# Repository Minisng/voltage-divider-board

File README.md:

[프로젝트 보고서] Voltage Divider Board Design & Simulation
1. Project Overview (프로젝트 개요)
목적: 10V DC 입력 전원을 받아 안정적인 2V DC 전압을 출력하는 전압 분배 회로 설계 및 PCB 제작 데이터 구축
주요 사양:
Input Voltage ($V_{in}$): 10V DC
Target Output Voltage ($V_{out}$): 2.0V DC
Load Resistance ($R_1, R_2$): $R_1 = 8\text{k}\Omega$, $R_2 = 2\text{k}\Omega$
사용 툴: LTspice (Simulation), KiCad 8.0 (Schematic & Layout)
2. Circuit Theory & LTspice Simulation (시뮬레이션 및 검증)
① 전압 분배 수식 검증
$$V_{out} = V_{in} \times \frac{R_2}{R_1 + R_2} = 10\text{V} \times \frac{2\text{k}\Omega}{8\text{k}\Omega + 2\text{k}\Omega} = 2.0\text{V}$$
② LTspice Transient Analysis
시뮬레이션 조건: .tran 1s (1초간 과도 응답 관찰)
결과분석: 10V DC 입력 조건에서 $V_{out}$ 노드가 오차 없이 정확히 2.0000V로 수렴함을 확인.
[첨부 1]: LTspice 회로도 및 파형 캡처 이미지 (앞서 캡처한 V(vout) = 2.0V 빨간선 그래프 이미지)
3. KiCad Schematic & PCB Layout (회로도 및 PCB 설계)
① Schematic Design
외부 전원 연결용 커넥터(J1, J2 2-Pin Header) 추가 및 ERC(Electrical Rules Check) 통과
Net Label (Vout) 설정을 통한 노드 식별성 강화
② PCB Layout Specifications
Board Dimensions: 2-Layer PCB (약 30mm x 20mm)
Component Footprints:
$R_1, R_2$: SMD 0805 Package
$J_1, J_2$: 2.54mm Pitch Pin Header
Copper Pour: Top/Bottom Layer 전체 GND Zone Fill (노이즈 방지)
DRC (Design Rules Check): 에러/미연결 패턴 0건 검수 완료
4. 3D Raytracing & Physical Verification (3D 검수 및 결과물)
[첨부 2]: KiCad 3D Viewer로 추출한 고화질 PCB 3D 렌더링 이미지 (Alt + 1 Top View, 사선 각도 뷰)
부품 배치 검수: 커넥터 및 저항 간 물리적 간섭(Clearance) 없음 확인
5. Deliverables (최종 산출물 목록)
Schematic & PCB File: KiCad 프로젝트 원본 파일
Gerber & Drill Files: 제조 공장 발주용 표준 데이터 (Gerber_VoltageDivider.zip)
Bill of Materials (BOM): 부품 목록 및 풋프린트 명세서 (CSV)

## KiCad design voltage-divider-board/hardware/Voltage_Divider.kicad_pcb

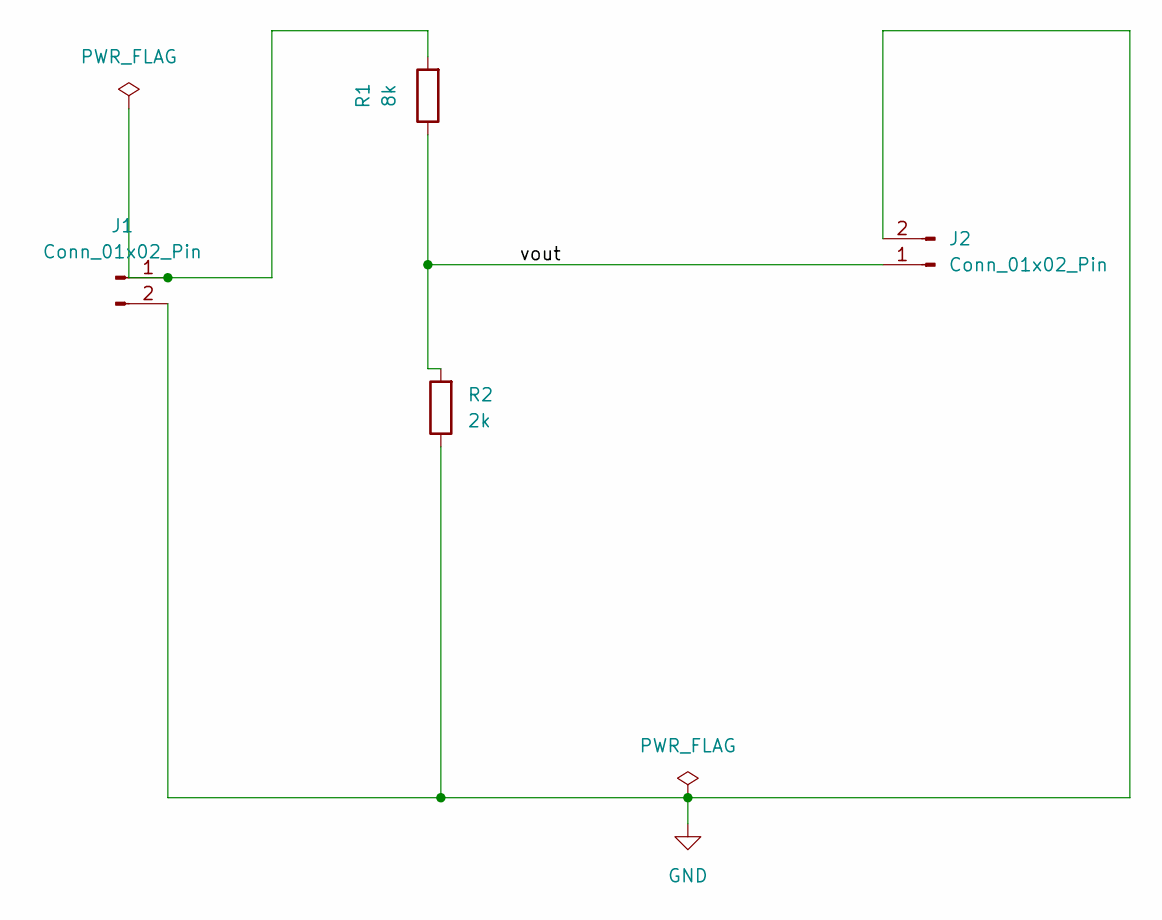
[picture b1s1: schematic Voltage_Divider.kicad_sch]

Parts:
J1: Conn_01x02_Pin; R_0805_2012Metric
J2: Conn_01x02_Pin; R_Axial_DIN0207_L6.3mm_D2.5mm_P7.62mm_Horizontal
R1: 8k; PinHeader_1x02_P2.54mm_Vertical
R2: 2k; PinHeader_1x02_P2.54mm_Vertical

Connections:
/vout: J2.1, R1.1, R2.2
GND: J1.2, J2.2, R2.1
unnamed: J1.1, R1.2

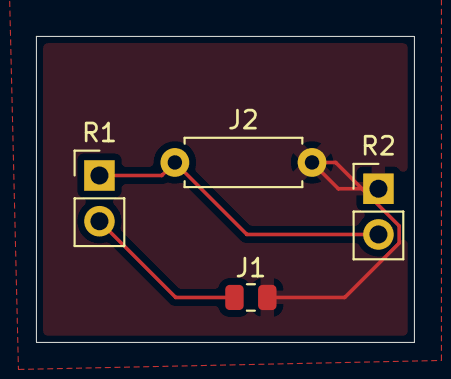
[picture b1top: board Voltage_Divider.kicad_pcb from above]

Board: 2 copper layers, 21.0 x 17.0 mm, 4 parts (0 on the bottom side), 3 nets.
